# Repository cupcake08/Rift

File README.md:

<div align="center">
    
</div>

Rift is a 34-key wireless low profile split keyboard featuring Nice!View/OLED display ,Rotary Encoder (EC11/EC12) and optional trackpad support. It runs on [ZMK](https://zmk.dev/) firmware and is powered by the [Seeed Xiao nRF52840](https://www.seeedstudio.com/Seeed-XIAO-BLE-nRF52840-p-5201.html) board.

It also has a dedicated [Sort-Off](https://zmk.dev/docs/features/soft-off) switch.

## Keyboard Images
| Description | Photo |
| :--: | :--: |
| Left and Right half |  |
| With [KLP Lamé](https://github.com/braindefender/KLP-Lame-Keycaps/blob/master/README.md)  keycaps |  |
| With Kailh V1 LP switches |  |
| No keycaps and switches on Left half |  |

*These images are from cad
## PCB Images
| Description                 | Front                                             | Back                                               |
| :--:                  | :--:                                              | :--:                                               |
| Keyboard PCB Front    |         |           |
| Xiao Extension        |  |  |

### Inspiration
- [Ferris(Sweep)](https://github.com/davidphilipbarr/Sweep)

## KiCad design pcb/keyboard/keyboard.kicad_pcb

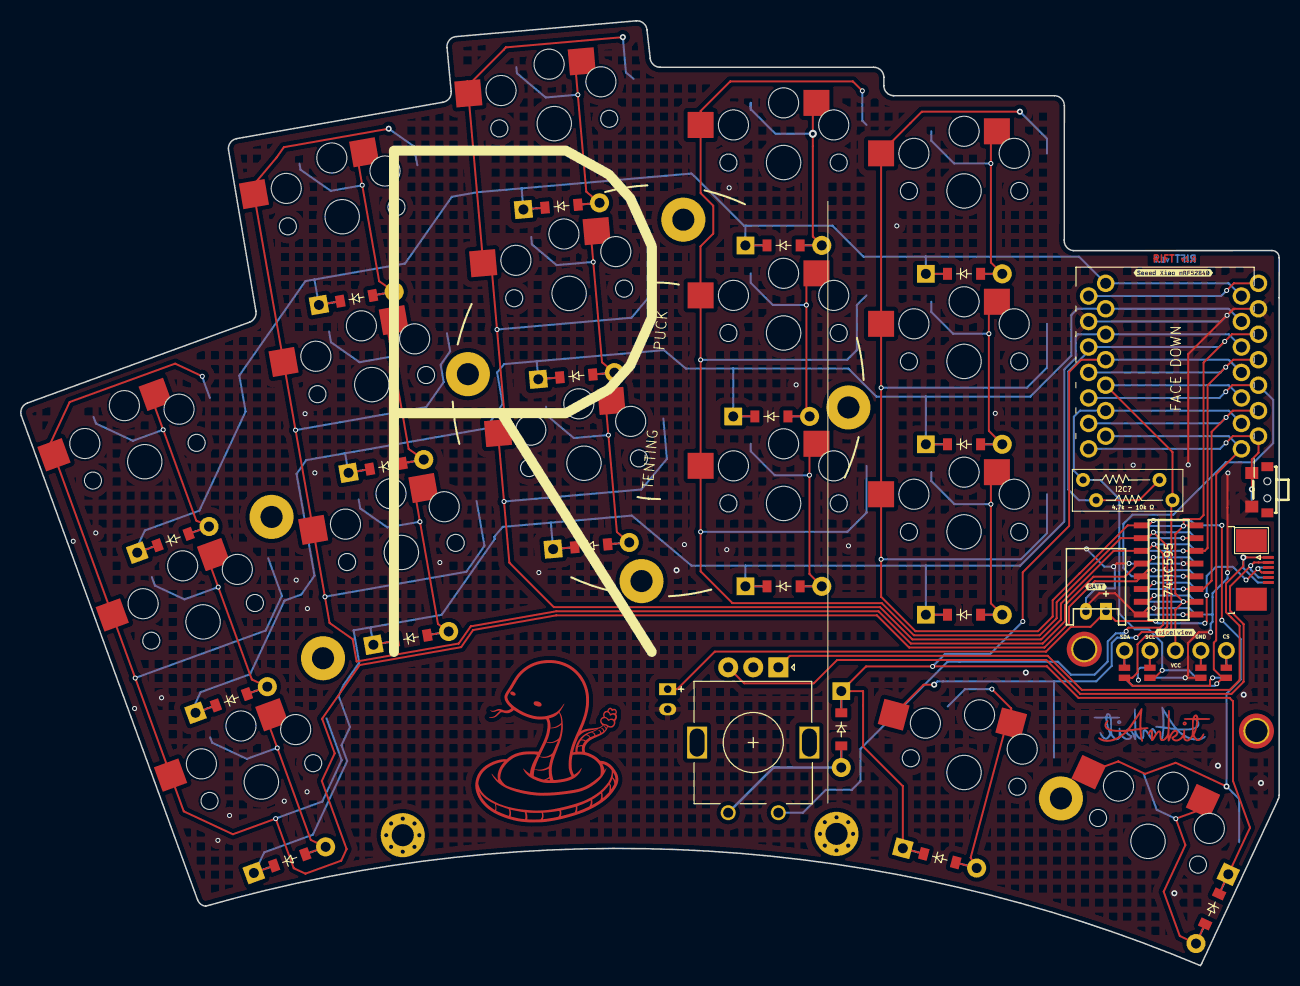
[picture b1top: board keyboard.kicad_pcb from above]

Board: 2 copper layers, 125.5 x 94.2 mm, 51 parts (1 on the bottom side), 44 nets.

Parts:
74HC595, 74HC595#2: VAL**; SOIC16
D1, D2, D3, D4, D5, D6, D7, D8, D9, D10, D11, D12, D13, D14, D15, D16, D17, D18: ComboDiode
JST1, JST1#2: JST_XH_S2B-XH-K_02x2.54mm_Angled
Nice!View1: niceview_headers
ROT1: rotary_encoder
S1, S2, S3, S4, S5, S6, S7, S8, S9, S10, S11, S12, S13, S14, S15, S16, S17: PG1350
U?: Seeed Xiao; XiaoBle
U?#2: Seeed Xiao; XiaoBle
_1: Tenting Puck
_2, _3, _4, _5: MountingHole_2.2mm_M2_Pad_Via
kibuzzard-6618164F: G***; kibuzzard-6618164F
kibuzzard-66181547: G***; kibuzzard-66181547
kibuzzard-66181572: G***; kibuzzard-66181572

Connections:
BAT: JST1.1, JST1#2.1
ENC: D18.2, ROT1.2
GND: 74HC595.8, 74HC595.13, 74HC595#2.8, 74HC595#2.13, JST1.2, JST1#2.2, Nice!View1.2, ROT1.C, U?.13, U?#2.13
P0: D3.1, D6.1, D9.1, D12.1, D15.1, U?.1, U?#2.1
P1: D2.1, D5.1, D8.1, D11.1, D14.1, U?.2, U?#2.2
P2: D1.1, D4.1, D7.1, D10.1, D13.1, U?.3, U?#2.3
P3: D16.1, D17.1, D18.1, U?.4, U?#2.4
P4: Nice!View1.2, U?.5, U?#2.5
P5: Nice!View1.2, U?.6, U?#2.6
P6: Nice!View1.2, U?.7, U?#2.7
P7: U?.8, U?#2.8
P8: 74HC595.11, 74HC595#2.11, U?.9, U?#2.9
P9: 74HC595.12, 74HC595#2.12, U?.10, U?#2.10
P10: 74HC595.14, 74HC595#2.14, U?.11, U?#2.11
Q0: 74HC595.15, 74HC595#2.15
Q1: 74HC595.1, 74HC595#2.1, S13.2, S14.2, S15.2, S17.2
Q2: 74HC595.2, 74HC595#2.2, S10.2, S11.2, S12.2, S16.2
Q3: 74HC595.3, 74HC595#2.3, ROT1.1, S7.2, S8.2, S9.2
Q4: 74HC595.4, 74HC595#2.4, S4.2, S5.2, S6.2
Q5: 74HC595.5, 74HC595#2.5, S1.2, S2.2, S3.2
Q6: 74HC595.6, 74HC595#2.6
Q7: 74HC595.7, 74HC595#2.7
Q7S: 74HC595.9, 74HC595#2.9
SCL: Nice!View1.1, Nice!View1.3
SDA: Nice!View1.1, Nice!View1.4
VCC: 74HC595.10, 74HC595.16, 74HC595#2.10, 74HC595#2.16, Nice!View1.2, U?.12, U?#2.12
VCC_5V: U?.14, U?#2.14
index_bottom: D10.2, S10.1
index_home: D11.2, S11.1
index_top: D12.2, S12.1
inner_bottom: D13.2, S13.1
inner_cluster: D16.2, S16.1
inner_home: D14.2, S14.1
inner_top: D15.2, S15.1
middle_bottom: D7.2, S7.1
middle_home: D8.2, S8.1
middle_top: D9.2, S9.1
outer_cluster: D17.2, S17.1
pinky_bottom: D1.2, S1.1
pinky_home: D2.2, S2.1
pinky_top: D3.2, S3.1
ring_bottom: D4.2, S4.1
ring_home: D5.2, S5.1
ring_top: D6.2, S6.1

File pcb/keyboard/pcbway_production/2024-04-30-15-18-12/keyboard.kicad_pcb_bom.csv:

designator,quantity,value,pack,mpn,mount_type
", ",2,,TE_0-1734839-6_1x06-1MP_P0.5mm_Horizontal,,tht
"74HC595, 74HC595",2,VAL**,SOIC16,,smt
"D1, D10, D11, D12, D13, D14, D15, D16, D17, D18, D2, D3, D4, D5, D6, D7, D8, D9",18,,ComboDiode,,tht
"JST1, JST1",2,,JST_XH_S2B-XH-K_02x2.54mm_Angled,,tht
Nice!View1,1,,niceview_headers,,tht
ROT1,1,,rotary_encoder,,tht
"S1, S10, S11, S12, S13, S14, S15, S16, S17, S2, S3, S4, S5, S6, S7, S8, S9",17,,PG1350,,tht
"U?, U?",2,Seeed Xiao,XiaoBle,,tht
_1,1,Tenting Puck,Tenting Puck,,tht
"_2, _3, _4, _5",4,,MountingHole_2.2mm_M2_Pad_Via,,tht
kibuzzard-66181547,1,G***,kibuzzard-66181547,,tht
kibuzzard-66181572,1,G***,kibuzzard-66181572,,tht
kibuzzard-6618164F,1,G***,kibuzzard-6618164F,,tht

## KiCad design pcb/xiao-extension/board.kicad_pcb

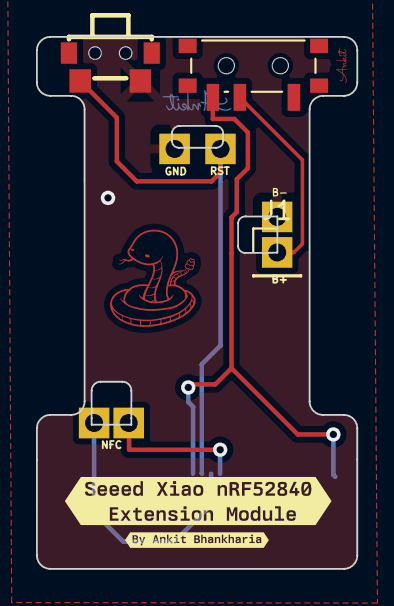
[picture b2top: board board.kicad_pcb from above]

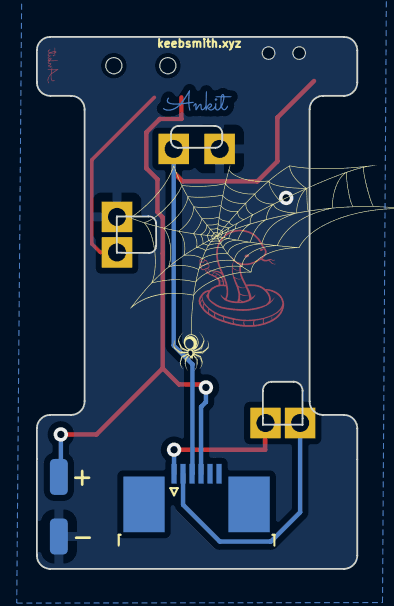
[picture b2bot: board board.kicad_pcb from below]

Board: 2 copper layers, 17.8 x 29.6 mm, 13 parts (3 on the bottom side), 6 nets.

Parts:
J1, J2, J3, J4: Conn_01x01_Pin; PinHeader_1x01_P2.54mm_Vertical
J5, J6: Conn_01x01_Pin; SolderWirePad_1x01_SMD_1x2mm
J8, J9: Conn_01x01; PinHeader_1x01_P2.54mm_Vertical
J10: Conn_01x05; TE_0-1734839-6_1x06-1MP_P0.5mm_Horizontal
SW2: SW_SPDT; SW_SPDT_PCM12
U2: TS24CA; TC24CA
kibuzzard-661B5F0D: G***; kibuzzard-661B5F0D
kibuzzard-661B5F47: G***; kibuzzard-661B5F47

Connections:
BAT_+: J1.1, SW2.2 (B)
BAT_++: J5.1, J10.4, SW2.3 (C)
ENC_A: J8.1, J10.1
ENC_B: J9.1, J10.2
GND: J2.1, J4.1, J6.1, U2.3
RST: J3.1, J10.3, U2.4

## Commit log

2024-04-12 pcb setup
2024-04-12 added gerbers
2024-04-18 directory structure fix
2024-04-18 deleted unwanted directory
2024-04-18 Linked firmware repo
2024-04-18 readme update
2024-04-25 imp: pcb design change
2024-04-25 add: pcb images
2024-04-25 update: firmware
2024-04-25 fix: firmware submodule
2024-04-26 add: keyboard demo pictures
2024-04-27 add: i2c resistor pull resistor
2024-04-27 add: i2c pull-up resistors and name on silkscreen
2024-04-27 add: more keyboard renders
2024-04-29 add: 3D models
2024-04-29 add: 3DP case
2024-04-29 firmware setup
2024-04-30 add: sponsorship.md
2024-04-30 update: README.md
